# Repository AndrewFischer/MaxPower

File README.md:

# MaxPower
MaxPower is a dual output buck/boot converter based on the LTC3130. <br>
Input power is from an on-board 18650 cell. Outputs are 5V and 3.3V. Other voltage pairs are possible. Maximum output current is 600mA.<br> 
An on-board chager is new for version 0.3. The charger is based on the [TP4056](https://jlcpcb.com/partdetail/17264-TP4056_42ESOP8/C16581), a linear constant-current/constant-voltage charger for a single LiIon battery. Charge current is set by R9. 2K gives about 580mA. The chip is rated to 1A, but I doubt the small PCB heatsink is large enough for 1A operation. Constant voltage operation starts when the battery reaches 4.2V. Charge terminates at C/10, about 58mA with R9 set to 2K.<br>
Charger absolute maxium input is 8VDC. 5V is a reasonable input voltage. 
The manufacturer datasheet and webpage for the TP4056 are in Chinese. I used Google Translate, then later found a third-party translation of the datasheet which you will find in the Datasheets folder. <br>
:warning: **There is no reverse polarity protection** Putting the battery in backwards will destroy the TP456. <br>
The external power input can only charge the battery. A TP4056 by itself can not properly charge a battery under load. Switch SW1 ensures the battery charger is only connected when the supply is off. TBD: Load sharing instead of the switch.<br> 
:warning: The files embodied in this repository are provided to you "as-is" and without warranty of any kind, express, implied or otherwise, including without limitation, any warranty of fitness for a particular purpose. See section 5 of the license. <br>
**This fork is an untested work in progress.** 

### License
[CC BY-NC 4.0](LICENSE.md)

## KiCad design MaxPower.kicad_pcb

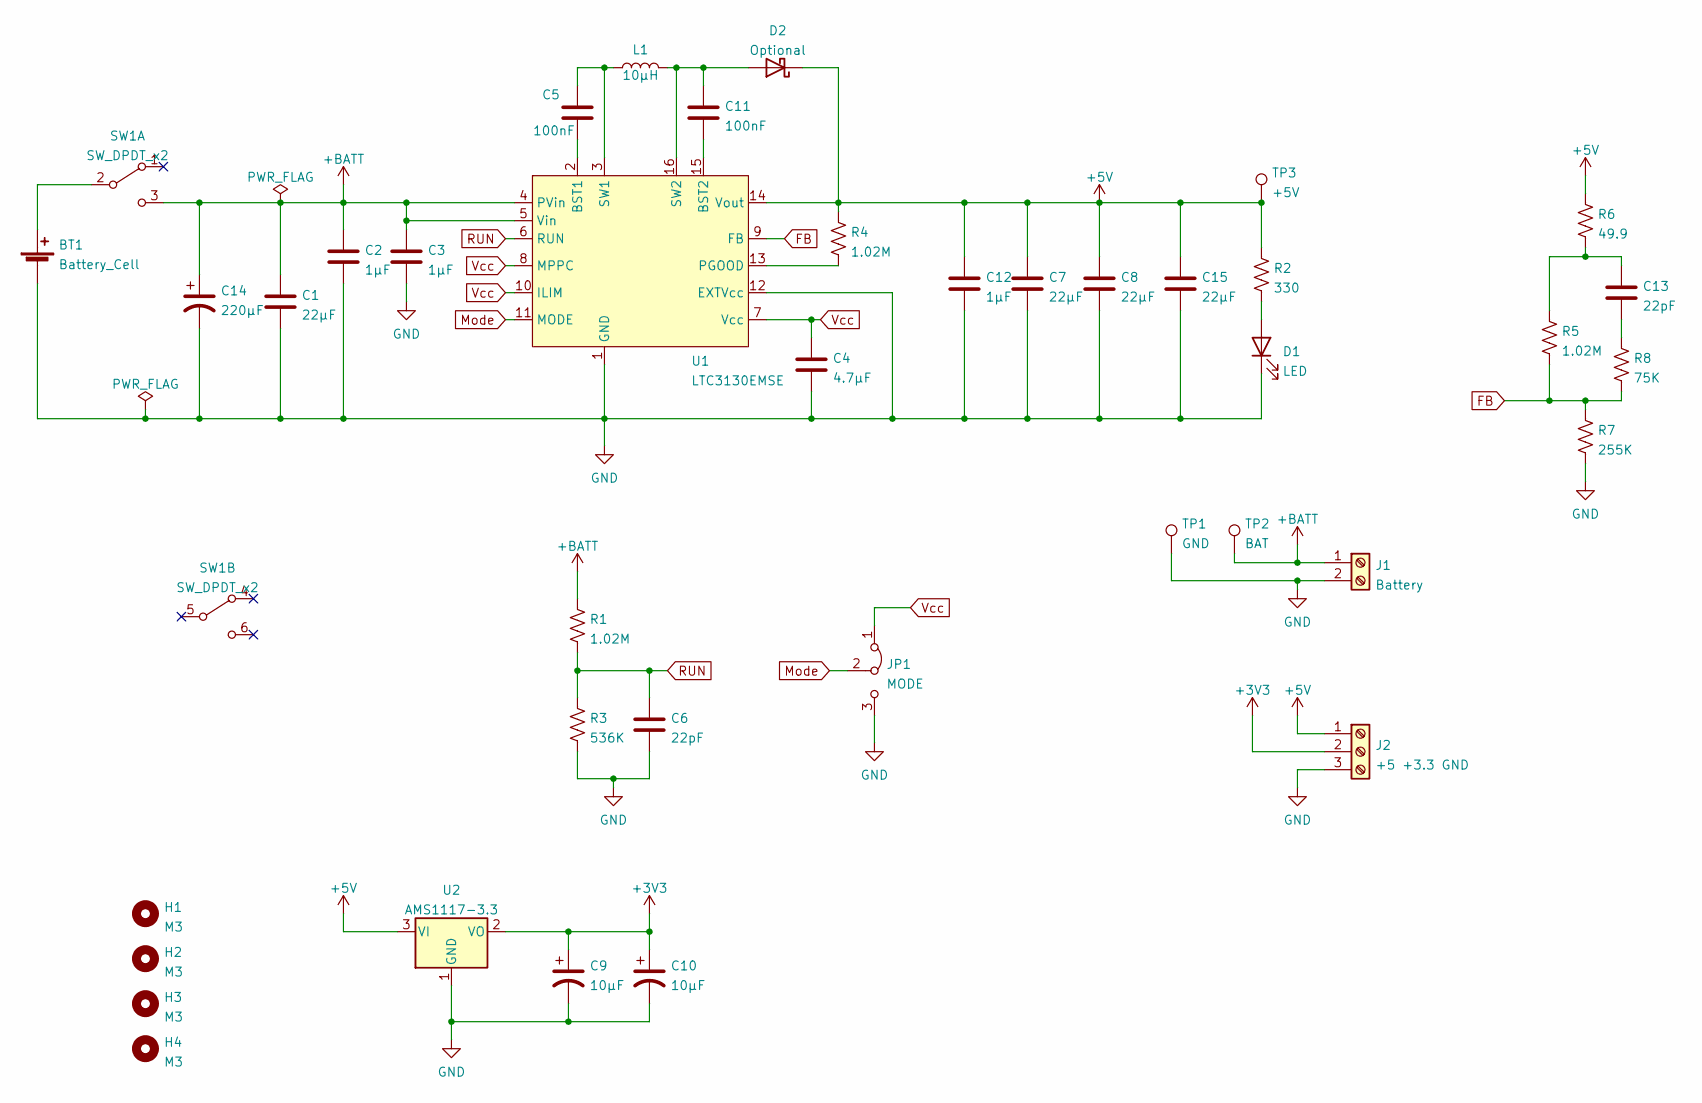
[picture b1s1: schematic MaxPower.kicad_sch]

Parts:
BT1: Battery_Cell; BatteryHolder_MPD_BH-18650-PC2
C1, C7, C8, C15: 22µF; C_1210_3225Metric; MPN GRM32ER71E226KE15L; LCSC C21397
C2, C3, C12: 1µF; C_0805_2012Metric; MPN CL21B105KBFNNNE; LCSC C28323
C4: 4.7µF; C_0603_1608Metric; MPN GRM188R60J475KE19D; LCSC C71631
C5: 100nF; C_0603_1608Metric; MPN CC0603KRX7R9BB104; LCSC C14663
C6, C13: 22pF; C_0603_1608Metric; MPN CL10C220JB8NNNC; LCSC C1653
C9, C10: 10µF; CP_EIA-3216-18_Kemet-A; LCSC C7171
C11: 100nF; C_0603_1608Metric; LCSC C14663
C14: 220µF; CP_Radial_D8.0mm_P3.50mm; MPN UPA1V271MPD
D1: LED; LED_D3.0mm
D2: Optional; D_SOD-123; MPN B5819W SL; LCSC C8598
H1, H2, H3, H4: M3; MountingHole_3.2mm_M3
J1: Battery; TerminalBlock_Phoenix_MKDS-1,5-2_1x02_P5.00mm_Horizontal
J2: +5 +3.3 GND; TerminalBlock_Phoenix_MKDS-1,5-3_1x03_P5.00mm_Horizontal
JP1: MODE; PinHeader_1x03_P2.54mm_Vertical
L1: 10µH; L_Coilcraft_XxL4030; MPN XGL4030-103
R1, R4, R5: 1.02M; R_0603_1608Metric; MPN RTT031024FTP; LCSC C166909
R2: 330; R_0805_2012Metric; MPN 0805W8F3300T5E; LCSC C17630
R3: 536K; R_0603_1608Metric; MPN 0603WAF5363T5E; LCSC C23200
R6: 49.9; R_0603_1608Metric; MPN 0603WAF499JT5E; LCSC C23185
R7: 255K; R_0603_1608Metric; MPN MCWF06R2553BTL; LCSC C241296
R8: 75K; R_0603_1608Metric; MPN 0603WAF7502T5E; LCSC C23242
SW1: SW_DPDT_x2; 2MD1
TP1: GND; PinHeader_1x01_P2.54mm_Vertical
TP2: BAT; PinHeader_1x01_P2.54mm_Vertical
TP3: +5V; PinHeader_1x01_P2.54mm_Vertical
U1: LTC3130EMSE; MSOP-16-1EP_3x4.039mm_P0.5mm_EP1.651x2.845mm
U2: AMS1117-3.3; SOT-223-3_TabPin2; LCSC C6186

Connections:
+3V3: C9.1, C10.1, J2.2, U2.2 (VO)
+5V: C7.1, C8.1, C12.1, C15.1, D2.1 (K), J2.1, R2.1, R4.1, R6.1, TP3.1, U1.14 (Vout), U2.3 (VI)
+BATT: C1.1, C2.1, C3.1, C14.1, J1.1, R1.1, SW1.3 (C), TP2.1, U1.4 (PVin), U1.5 (Vin)
FB: R5.2, R7.1, R8.2, U1.9 (FB)
GND: BT1.2 (-), C1.2, C2.2, C3.2, C4.2, C6.2, C7.2, C8.2, C9.2, C10.2, C12.2, C14.2, C15.2, D1.1 (K), J1.2, J2.3, JP1.3 (B), R3.2, R7.2, TP1.1, U1.1 (GND), U1.12 (EXTVcc), U1.17 (GND), U2.1 (GND)
Mode: JP1.2 (C), U1.11 (MODE)
unnamed: BT1.1 (+), SW1.2 (B)
unnamed: C5.1, L1.1, U1.3 (SW1)
unnamed: C5.2, U1.2 (BST1)
unnamed: C11.1, D2.2 (A), L1.2, U1.16 (SW2)
unnamed: C11.2, U1.15 (BST2)
unnamed: C13.1, R5.1, R6.2
unnamed: C13.2, R8.1
unnamed: D1.2 (A), R2.2
unnamed: R4.2, U1.13 (PGOOD)
RUN: C6.1, R1.2, R3.1, U1.6 (RUN)
Vcc: C4.1, JP1.1 (A), U1.7 (Vcc), U1.8 (MPPC), U1.10 (ILIM)

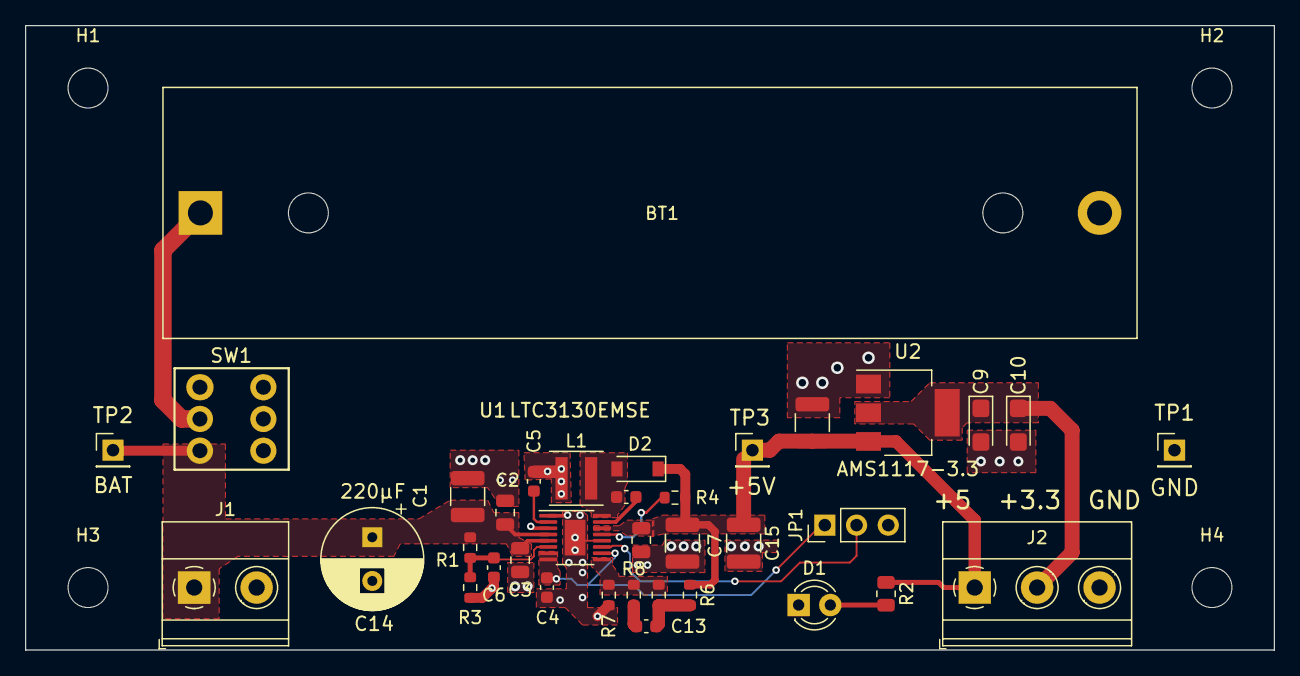
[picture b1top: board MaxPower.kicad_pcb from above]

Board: 2 copper layers, 100.0 x 50.0 mm, 40 parts (0 on the bottom side), 17 nets.

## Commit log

2023-03-13 Fill out README
2023-03-17 Add license
2023-04-07 Add TP4056 battery charger IC to symbol library
2023-04-08 Update to kicad 7. Add CC license to drawing.
2023-04-10 Add TP4056 battery charger to schematic and README
2023-04-10 Add disclaimers
2023-04-11 Minor cleanup of Readme
2023-04-13 Updates
    Updates
2023-04-14 Add footprint and LCSC part numbers.

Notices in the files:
MaxPower.kicad_pcb:
Copyright 2022  Andrew Fischer
